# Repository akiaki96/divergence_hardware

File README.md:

# divergence_hardware
クラシックマウス「発散値」のハードウェアです．

[テクニカルデータシート](https://www.ntf.or.jp/entry/2026/RobotEnt03.php?n&id=370755)

[ソースコード](https://github.com/akiaki96/divergence_v3)

いつかハードウェアの解説記事を書こうと思っています．  
ソフトウェアの解説記事は[こちら](https://qiita.com/akiaki96/items/6498b00ca979ef92b548)です．

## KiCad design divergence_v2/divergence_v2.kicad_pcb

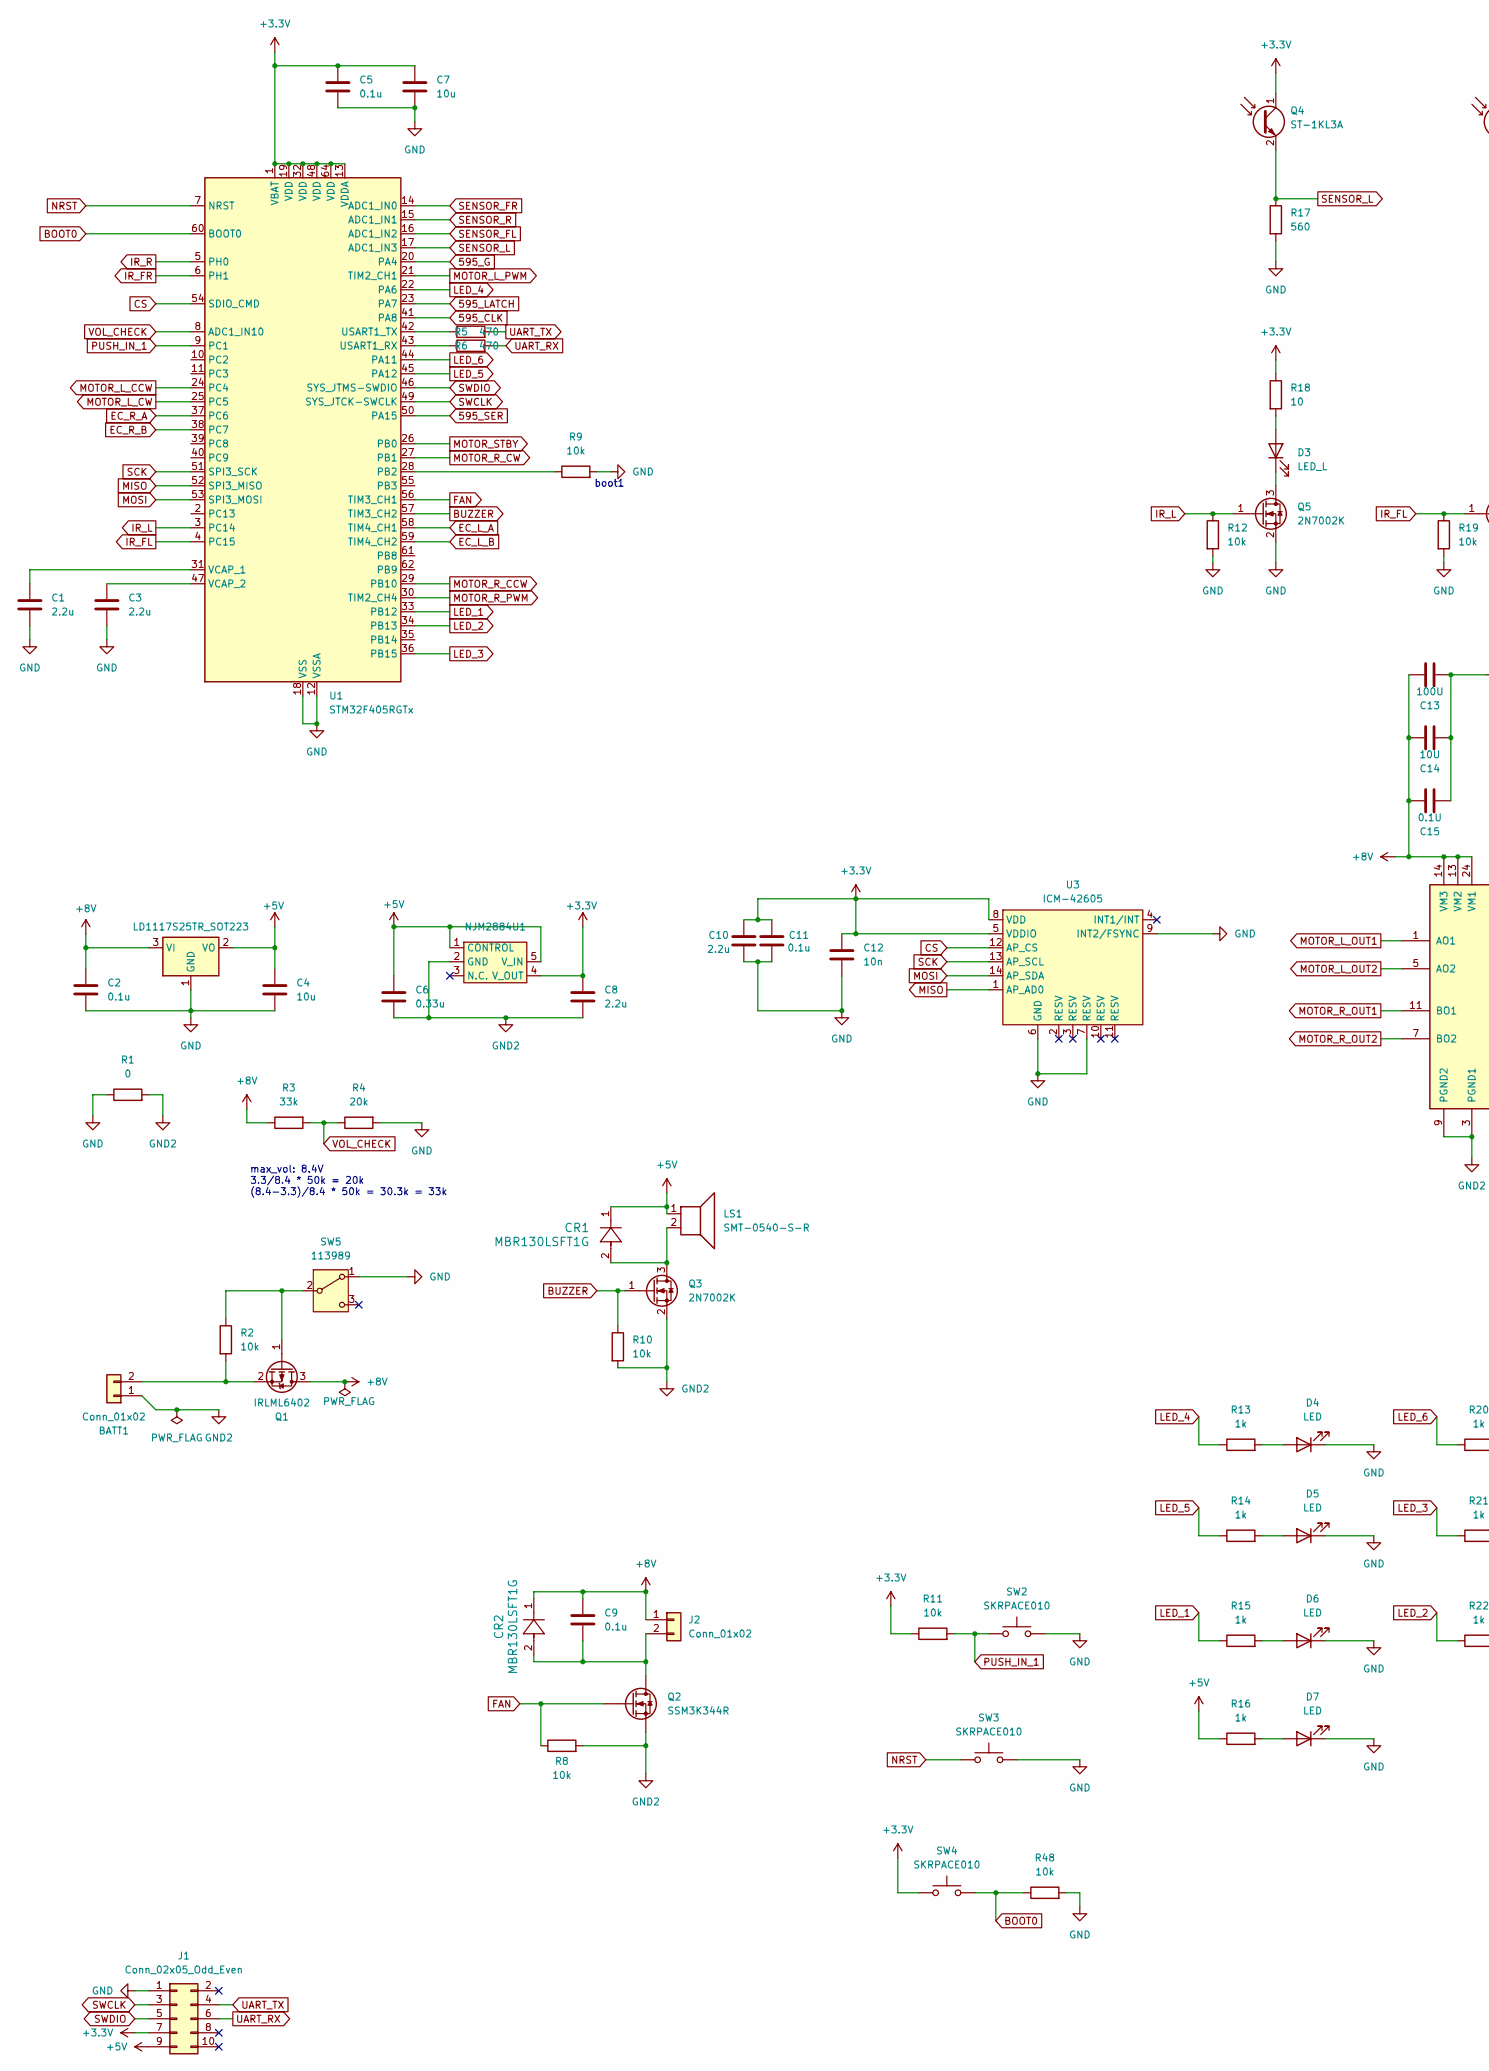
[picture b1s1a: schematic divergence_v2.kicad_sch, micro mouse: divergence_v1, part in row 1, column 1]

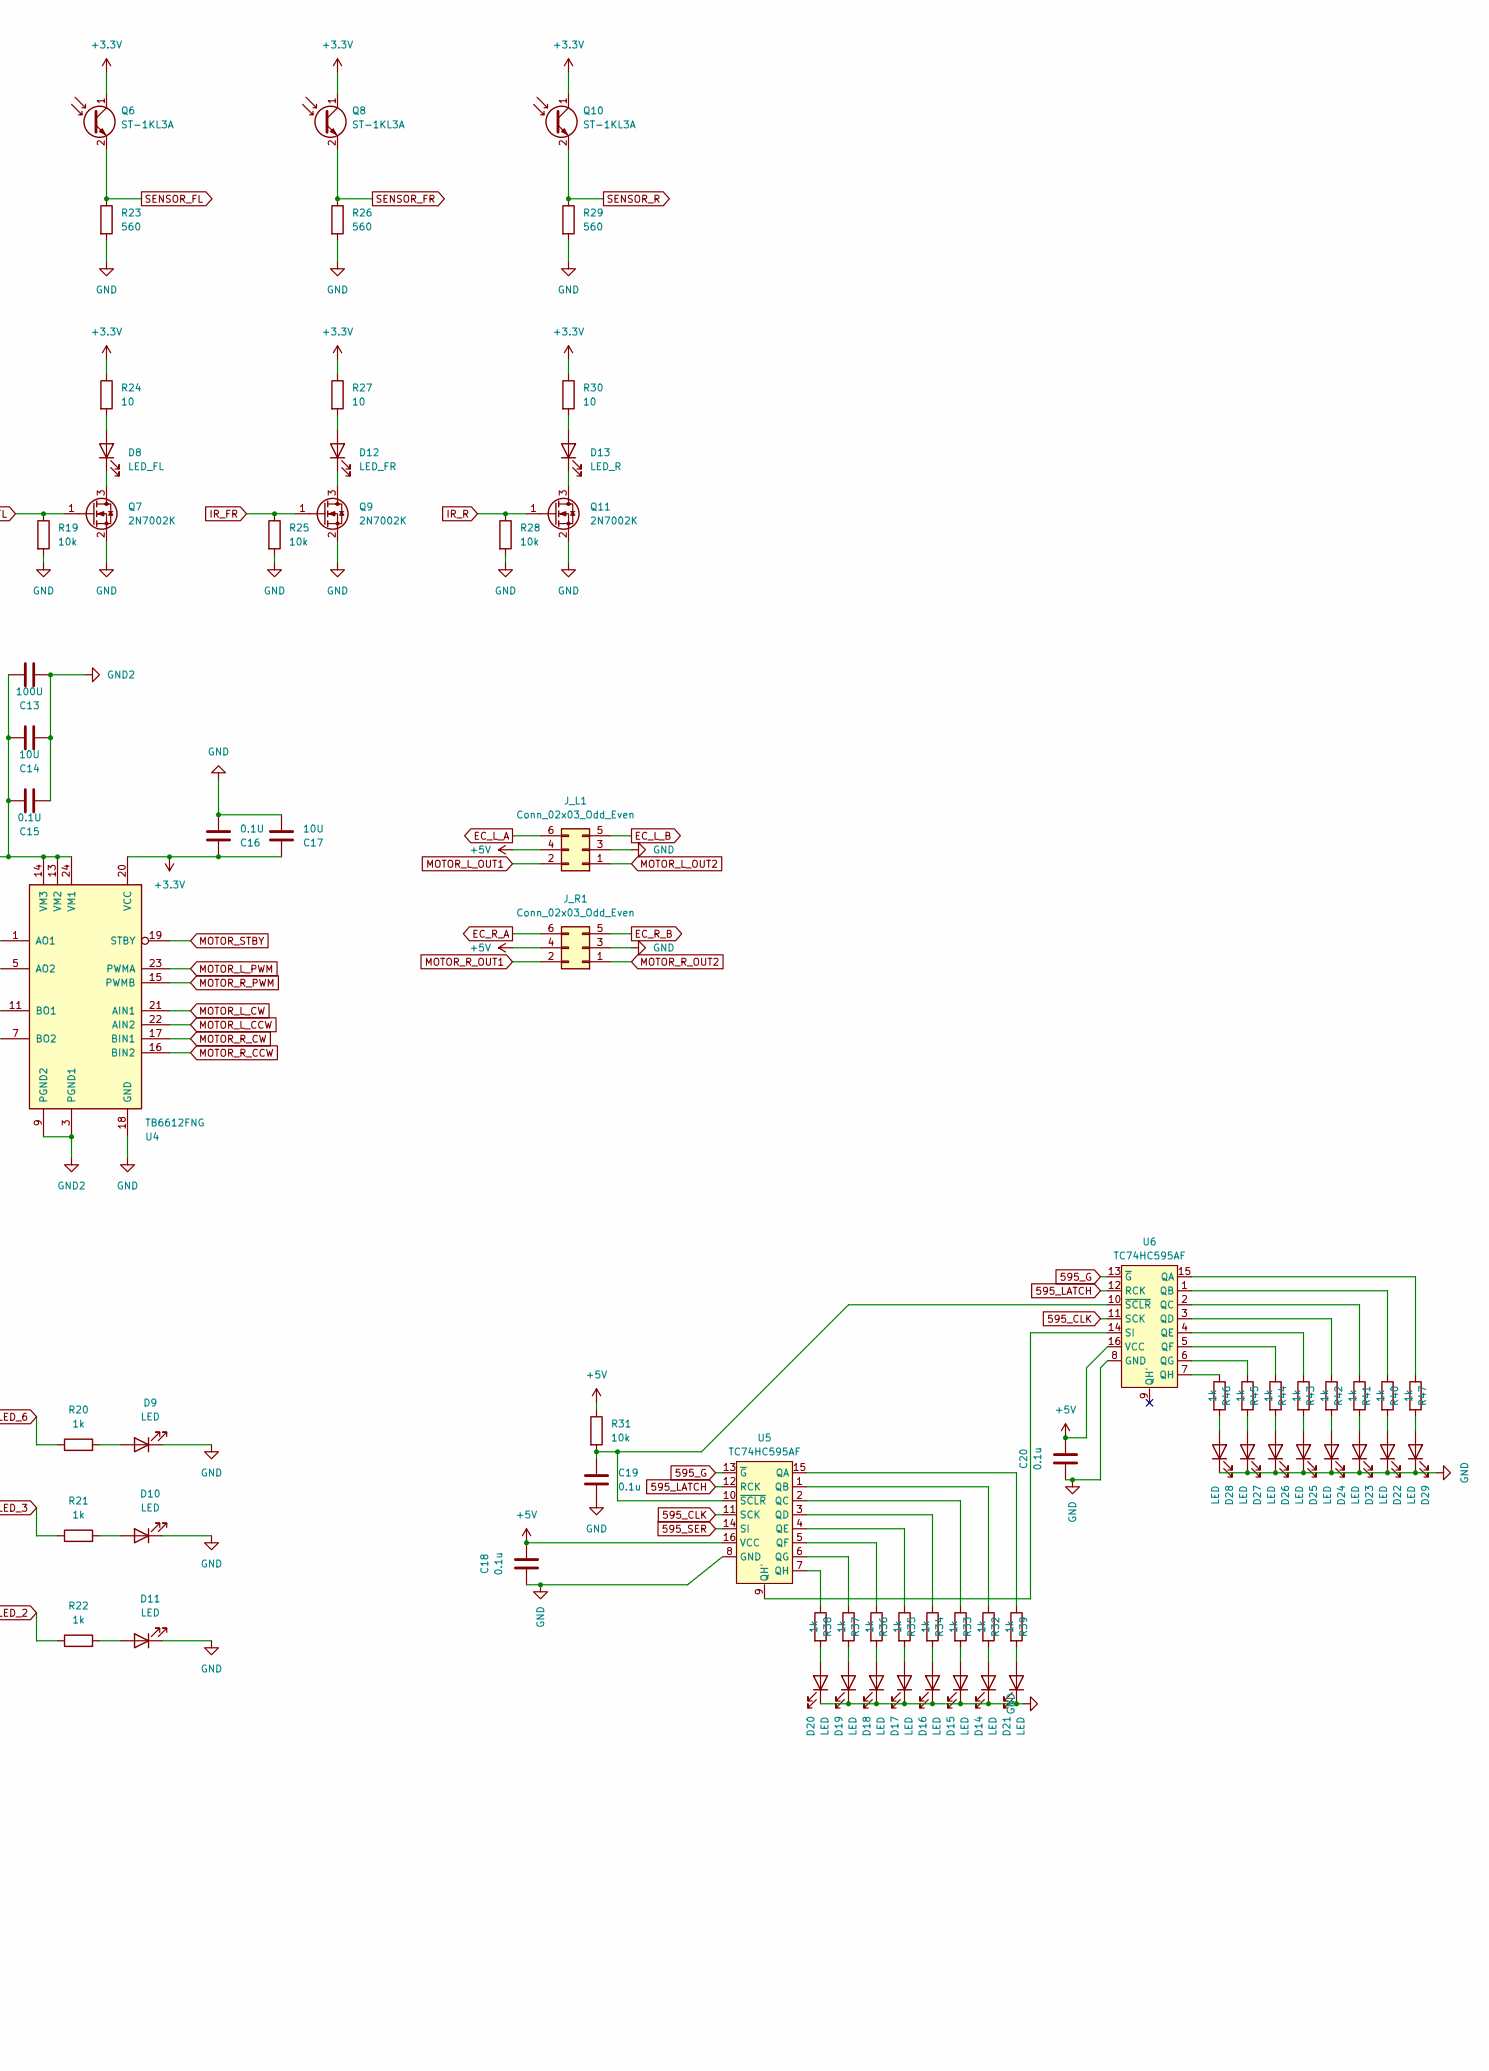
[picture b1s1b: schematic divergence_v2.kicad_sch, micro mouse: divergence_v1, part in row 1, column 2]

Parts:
BATT1: Conn_01x02; PinHeader_1x02_P2.54mm_Vertical
C1, C3, C8, C10: 2.2u; C_0603_1608Metric_Pad1.08x0.95mm_HandSolder
C2, C5, C9, C11, C18, C19, C20: 0.1u; C_0603_1608Metric_Pad1.08x0.95mm_HandSolder
C4, C7: 10u; C_0603_1608Metric_Pad1.08x0.95mm_HandSolder
C6: 0.33u; C_0603_1608Metric_Pad1.08x0.95mm_HandSolder
C12: 10n; C_0603_1608Metric_Pad1.08x0.95mm_HandSolder
C13: 100U; C_1206_3216Metric_Pad1.33x1.80mm_HandSolder
C14, C17: 10U; C_0603_1608Metric_Pad1.08x0.95mm_HandSolder
C15, C16: 0.1U; C_0603_1608Metric_Pad1.08x0.95mm_HandSolder
CR1, CR2: MBR130LSFT1G; DIODE_SOD123LF_2P9X1P8_ONS
D3: LED_L; LED_D4.0mm
D4, D5, D6, D7, D9, D10, D11, D14, D15, D16, D17, D18, D19, D20, D21, D22, D23, D24, D25, D26, D27, D28, D29: LED; LED_0603_1608Metric_Pad1.05x0.95mm_HandSolder
D8: LED_FL; LED_D4.0mm
D12: LED_FR; LED_D4.0mm
D13: LED_R; LED_D4.0mm
J1: Conn_02x05_Odd_Even; PinHeader_2x05_P1.27mm_Vertical_SMD
J2: Conn_01x02; PinHeader_1x02_P1.27mm_Vertical
J_L1: Conn_02x03_Odd_Even; PinHeader_2x03_P2.54mm_Vertical
J_R1: Conn_02x03_Odd_Even; PinHeader_2x03_P2.54mm_Vertical
LD1: LD1117S25TR_SOT223; SOT-223-3_TabPin2
LS1: SMT-0540-S-R
Q1: IRLML6402; SOT-23_Handsoldering
Q2: SSM3K344R; SOT-23F
Q3, Q5, Q7, Q9, Q11: 2N7002K; SOT-23
Q4, Q6, Q8, Q10: ST-1KL3A; D_DO-34_SOD68_P2.54mm_Vertical_AnodeUp
R1: 0; R_0603_1608Metric_Pad0.98x0.95mm_HandSolder
R2, R8, R9, R10, R11, R12, R19, R25, R28, R31, R48: 10k; R_0603_1608Metric_Pad0.98x0.95mm_HandSolder
R3: 33k; R_0603_1608Metric_Pad0.98x0.95mm_HandSolder
R4: 20k; R_0603_1608Metric_Pad0.98x0.95mm_HandSolder
R5, R6: 470; R_0603_1608Metric_Pad0.98x0.95mm_HandSolder
R13, R14, R15, R16, R20, R21, R22, R32, R33, R34, R35, R36, R37, R38, R39, R40, R41, R42, R43, R44, R45, R46, R47: 1k; R_0603_1608Metric_Pad0.98x0.95mm_HandSolder
R17, R23, R26, R29: 560; R_0603_1608Metric_Pad0.98x0.95mm_HandSolder
R18, R24, R27, R30: 10; R_0603_1608Metric_Pad0.98x0.95mm_HandSolder
SW2, SW3, SW4: SKRPACE010; SW4_SKRPABE010_ALPS
SW5: 113989; SSAJ120100
U1: STM32F405RGTx; LQFP-64_10x10mm_P0.5mm
U2: NJM2884U1; SOT-89-5
U3: ICM-42605; LGA-14_3x2.5mm_P0.5mm_LayoutBorder3x4y
U4: TB6612FNG; SSOP-24_5.3x8.2mm_P0.65mm
U5, U6: TC74HC595AF; SOP16-P-300-1.27A

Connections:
595_CLK: U1.41 (PA8), U5.11 (SCK), U6.11 (SCK)
595_G: U1.20 (PA4), U5.13 (~G), U6.13 (~G)
595_LATCH: U1.23 (PA7), U5.12 (RCK), U6.12 (RCK)
595_SER: U1.50 (PA15), U5.14 (SI)
+3.3V: C5.2, C7.2, C8.1, C10.1, C11.1, C12.1, C16.1, C17.1, J1.7, Q4.1 (C), Q6.1 (C), Q8.1 (C), Q10.1 (C), R11.1, R18.1, R24.1, R27.1, R30.1, SW4.1, U1.1 (VBAT), U1.13 (VDDA), U1.19 (VDD), U1.32 (VDD), U1.48 (VDD), U1.64 (VDD), U2.4 (V_OUT), U3.5 (VDDIO), U3.8 (VDD), U4.20 (VCC)
+5V: C4.1, C6.1, C18.1, C20.1, CR1.1, J1.9, J_L1.4, J_R1.4, LD1.2 (VO), LS1.1, R16.1, R31.1, U2.1 (CONTROL), U2.5 (V_IN), U5.16 (VCC), U6.16 (VCC)
+8V: C2.1, C9.1, C13.1, C14.1, C15.1, CR2.1, J2.1, LD1.3 (VI), Q1.3 (D), R3.1, U4.13 (VM2), U4.14 (VM3), U4.24 (VM1)
BOOT0: R48.1, SW4.2, U1.60 (BOOT0)
BUZZER: Q3.1 (G), R10.1, U1.57 (TIM3_CH2)
CS: U1.54 (SDIO_CMD), U3.12 (AP_CS)
EC_L_A: J_L1.6, U1.58 (TIM4_CH1)
EC_L_B: J_L1.5, U1.59 (TIM4_CH2)
EC_R_A: J_R1.6, U1.37 (PC6)
EC_R_B: J_R1.5, U1.38 (PC7)
FAN: Q2.G, R8.1, U1.56 (TIM3_CH1)
GND: C1.2, C2.2, C3.1, C4.2, C5.1, C7.1, C10.2, C11.2, C12.2, C16.2, C17.2, C18.2, C19.2, C20.2, D4.1 (K), D5.1 (K), D6.1 (K), D7.1 (K), D9.1 (K), D10.1 (K), D11.1 (K), D14.1 (K), D15.1 (K), D16.1 (K), D17.1 (K), D18.1 (K), D19.1 (K), D20.1 (K), D21.1 (K), D22.1 (K), D23.1 (K), D24.1 (K), D25.1 (K), D26.1 (K), D27.1 (K), D28.1 (K), D29.1 (K), J1.1, J_L1.3, J_R1.3, LD1.1 (GND), Q5.2 (S), Q7.2 (S), Q9.2 (S), Q11.2 (S), R1.1, R4.2, R9.2, R12.2, R17.2, R19.2, R23.2, R25.2, R26.2, R28.2, R29.2, R48.2, SW2.2, SW3.2, SW5.1 (A), U1.12 (VSSA), U1.18 (VSS), U1.63 (VSS), U3.6 (GND), U3.7 (RESV), U3.9 (INT2/FSYNC), U4.18 (GND), U5.8 (GND), U6.8 (GND)
GND2: BATT1.1, C6.2, C8.2, C13.2, C14.2, C15.2, Q2.S, Q3.2 (S), R1.2, R8.2, R10.2, U2.2 (GND), U4.3 (PGND1), U4.4 (PGND1), U4.9 (PGND2), U4.10 (PGND2)
IR_FL: Q7.1 (G), R19.1, U1.4 (PC15)
IR_FR: Q9.1 (G), R25.1, U1.6 (PH1)
IR_L: Q5.1 (G), R12.1, U1.3 (PC14)
IR_R: Q11.1 (G), R28.1, U1.5 (PH0)
LED_1: R15.1, U1.33 (PB12)
LED_2: R22.1, U1.34 (PB13)
LED_3: R21.1, U1.36 (PB15)
LED_4: R13.1, U1.22 (PA6)
LED_5: R14.1, U1.45 (PA12)
LED_6: R20.1, U1.44 (PA11)
MISO: U1.52 (SPI3_MISO), U3.1 (AP_AD0)
MOSI: U1.53 (SPI3_MOSI), U3.14 (AP_SDA)
MOTOR_L_CCW: U1.24 (PC4), U4.22 (AIN2)
MOTOR_L_CW: U1.25 (PC5), U4.21 (AIN1)
MOTOR_L_OUT1: J_L1.2, U4.1 (AO1), U4.2 (AO1)
MOTOR_L_OUT2: J_L1.1, U4.5 (AO2), U4.6 (AO2)
MOTOR_L_PWM: U1.21 (TIM2_CH1), U4.23 (PWMA)
MOTOR_R_CCW: U1.29 (PB10), U4.16 (BIN2)
MOTOR_R_CW: U1.27 (PB1), U4.17 (BIN1)
MOTOR_R_OUT1: J_R1.2, U4.11 (BO1), U4.12 (BO1)
MOTOR_R_OUT2: J_R1.1, U4.7 (BO2), U4.8 (BO2)
MOTOR_R_PWM: U1.30 (TIM2_CH4), U4.15 (PWMB)
MOTOR_STBY: U1.26 (PB0), U4.19 (STBY)
NRST: SW3.1, U1.7 (NRST)
unnamed: BATT1.2, Q1.2 (S), R2.2
unnamed: D3.2 (A), R18.2
unnamed: D3.1 (K), Q5.3 (D)
unnamed: D4.2 (A), R13.2
unnamed: D5.2 (A), R14.2
unnamed: D6.2 (A), R15.2
unnamed: D7.2 (A), R16.2
unnamed: D8.2 (A), R24.2
unnamed: D8.1 (K), Q7.3 (D)
unnamed: D9.2 (A), R20.2
unnamed: D10.2 (A), R21.2
unnamed: D11.2 (A), R22.2
unnamed: D12.2 (A), R27.2
unnamed: D12.1 (K), Q9.3 (D)
unnamed: D13.2 (A), R30.2
unnamed: D13.1 (K), Q11.3 (D)
unnamed: D14.2 (A), R32.2
unnamed: D15.2 (A), R33.2
unnamed: D16.2 (A), R34.2
unnamed: D17.2 (A), R35.2
unnamed: D18.2 (A), R36.2
unnamed: D19.2 (A), R37.2
unnamed: D20.2 (A), R38.2
unnamed: D21.2 (A), R39.2
unnamed: D22.2 (A), R40.2
unnamed: D23.2 (A), R41.2
unnamed: D24.2 (A), R42.2
unnamed: D25.2 (A), R43.2
unnamed: D26.2 (A), R44.2
unnamed: D27.2 (A), R45.2
unnamed: D28.2 (A), R46.2
unnamed: D29.2 (A), R47.2
unnamed: C9.2, CR2.2, J2.2, Q2.D
unnamed: Q1.1 (G), R2.1, SW5.2 (B)
unnamed: CR1.2, LS1.2, Q3.3 (D)
unnamed: R5.1, U1.42 (USART1_TX)
unnamed: R6.1, U1.43 (USART1_RX)
unnamed: R9.1, U1.28 (PB2)
unnamed: C1.1, U1.31 (VCAP_1)
unnamed: C3.2, U1.47 (VCAP_2)
unnamed: R39.1, U5.15 (QA)
unnamed: R32.1, U5.1 (QB)
unnamed: R33.1, U5.2 (QC)
unnamed: R34.1, U5.3 (QD)
unnamed: R35.1, U5.4 (QE)
unnamed: R36.1, U5.5 (QF)
unnamed: R37.1, U5.6 (QG)
unnamed: U5.9 (QH'), U6.14 (SI)
unnamed: R38.1, U5.7 (QH)
unnamed: C19.1, R31.2, U5.10 (~SCLR), U6.10 (~SCLR)
unnamed: R47.1, U6.15 (QA)
unnamed: R40.1, U6.1 (QB)
unnamed: R41.1, U6.2 (QC)
unnamed: R42.1, U6.3 (QD)
unnamed: R43.1, U6.4 (QE)
unnamed: R44.1, U6.5 (QF)
unnamed: R45.1, U6.6 (QG)
unnamed: R46.1, U6.7 (QH)
PUSH_IN_1: R11.2, SW2.1, U1.9 (PC1)
SCK: U1.51 (SPI3_SCK), U3.13 (AP_SCL)
SENSOR_FL: Q6.2 (E), R23.1, U1.16 (ADC1_IN2)
SENSOR_FR: Q8.2 (E), R26.1, U1.14 (ADC1_IN0)
SENSOR_L: Q4.2 (E), R17.1, U1.17 (ADC1_IN3)
SENSOR_R: Q10.2 (E), R29.1, U1.15 (ADC1_IN1)
SWCLK: J1.3, U1.49 (SYS_JTCK-SWCLK)
SWDIO: J1.5, U1.46 (SYS_JTMS-SWDIO)
UART_RX: J1.6, R6.2
UART_TX: J1.4, R5.2
VOL_CHECK: R3.2, R4.1, U1.8 (ADC1_IN10)

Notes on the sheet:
boot1
max_vol: 8.4V 3.3/8.4 * 50k = 20k (8.4-3.3)/8.4 * 50k = 30.3k = 33k

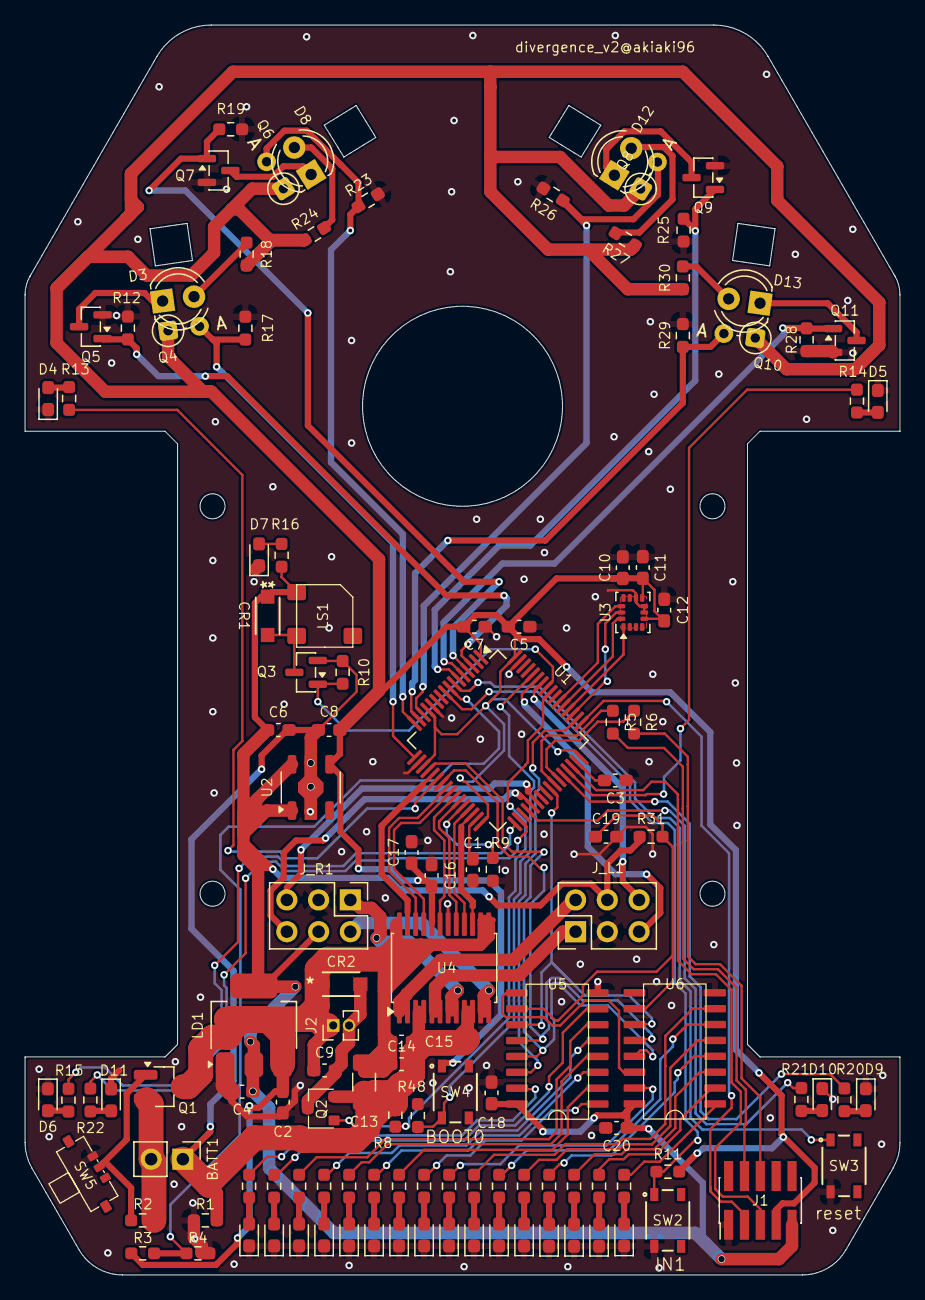
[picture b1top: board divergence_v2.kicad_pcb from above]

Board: 2 copper layers, 70.0 x 100.0 mm, 124 parts (0 on the bottom side), 110 nets.

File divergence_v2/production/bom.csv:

Designator,Footprint,Quantity,Value,LCSC Part #
BATT1,PinHeader_1x02_P2.54mm_Vertical,1,Conn_01x02,
"C1, C10, C3, C8",0603,4,2.2u,
"C11, C15, C16, C18, C19, C2, C20, C5, C9",0603,9,0.1u,
C12,0603,1,10n,
C13,1206,1,100U,
"C14, C17, C4, C7",0603,4,10U,
C6,0603,1,0.33u,
"CR1, CR2",DIODE_SOD123LF_2P9X1P8_ONS,2,MBR130LSFT1G,
"D10, D11, D14, D15, D16, D17, D18, D19, D20, D21, D22, D23, D24, D25, D26, D27, D28, D29, D4, D5, D6, D7, D9",0603,23,LED,
D12,LED_D4.0mm,1,LED_FR,
D13,LED_D4.0mm,1,LED_R,
D3,LED_D4.0mm,1,LED_L,
D8,LED_D4.0mm,1,LED_FL,
J1,PinHeader_2x05_P1.27mm_Vertical_SMD,1,Conn_02x05_Odd_Even,
J2,PinHeader_1x02_P1.27mm_Vertical,1,Conn_01x02,
"J_L1, J_R1",PinHeader_2x03_P2.54mm_Vertical,2,Conn_02x03_Odd_Even,
LD1,SOT-223-3_TabPin2,1,LD1117S25TR_SOT223,
LS1,SMT-0540-S-R,1,SMT-0540-S-R,
Q1,SOT-23_Handsoldering,1,IRLML6402,
"Q10, Q4, Q6, Q8",D_DO-34_SOD68_P2.54mm_Vertical_AnodeUp,4,ST-1KL3A,
"Q11, Q3, Q5, Q7, Q9",SOT-23,5,2N7002K,
Q2,SOT-23F,1,SSM3K344R,
R1,0603,1,0,
"R10, R11, R12, R19, R2, R25, R28, R31, R48, R8, R9",0603,11,10k,
"R13, R14, R15, R16, R20, R21, R22, R32, R33, R34, R35, R36, R37, R38, R39, R40, R41, R42, R43, R44, R45, R46, R47",0603,23,1k,
"R17, R23, R26, R29",0603,4,560,
"R18, R24, R27, R30",0603,4,10,
R3,0603,1,33k,
R4,0603,1,20k,
"R5, R6",0603,2,470,
"SW2, SW3, SW4",SW4_SKRPABE010_ALPS,3,SKRPACE010,
SW5,SSAJ120100,1,113989,
U1,LQFP-64_10x10mm_P0.5mm,1,STM32F405RGTx,
U2,SOT-89-5,1,NJM2884U1,
U3,LGA-14_3x2.5mm_P0.5mm_LayoutBorder3x4y,1,ICM-42605,
U4,SSOP-24_5.3x8.2mm_P0.65mm,1,TB6612FNG,
"U5, U6",SOP16-P-300-1.27A,2,TC74HC595AF,
